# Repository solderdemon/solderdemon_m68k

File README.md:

# SolderDemon m68k

## Overview

SolderDemon develops a line of Motorola 68k computers built from **through-hole (THT) parts**. This repository holds its mainboard: the board design, firmware, software and CPLD code. Expansion boards such as the [busboard](https://github.com/solderdemon/solderdemon_m68k-busboard) plug into its J3 expansion connector.

The mainboard is built on [rosco_m68k](https://github.com/rosco-m68k/rosco_m68k) by Ross Bamford, The Really Old-School Company Limited, and contributors. SolderDemon boards carry their own revision numbers, starting at r1; the rosco r2.x numbers are the history they grew from.

## Start here

- [KiCad project](design/solderdemon_m68k.kicad_pro)
- [Schematic (PDF)](manufacturing/solderdemon_m68k-r1-schematic.pdf)
- [Build guide](docs/README.md)
- [Fabrication package](manufacturing/solderdemon_m68k-r1-factory.zip)

### Find your way around

| What you need | Where to go |
| --- | --- |
| Board design | [design](design/README.md) |
| BOM, jumper settings, memory map, and expansion pinout | [docs](docs/README.md) |
| Firmware and ROM code | [code/firmware](code/firmware) |
| PLD source and programming | [PLD guide](code/firmware/pld/README.md) |
| Software, libraries, and examples | [code/software](code/software) |
| Recommended software workflow | [rosco CLI and Docker guide](docs/development.md) |
| Emulator for rosco_m68k and rosco_6502 | [SolderDemon rosco-emulator](https://github.com/solderdemon/rosco-emulator) |

## Board views

r1 is the current through-hole prototype. KiCad renders of it, top and bottom:

The current PCB and factory files use 23 radial ceramic 100 nF capacitors with 5.08 mm
lead spacing. The renders below predate that footprint change; use the current KiCad board
for placement and hole positions.

<details>
<summary>Photos from the project's early prototypes</summary>

These images show early project prototypes.

</details>

## Hardware

### The board: r1

| | |
| --- | --- |
| CPU | MC68010, 10 MHz |
| Memory | 1 MB Flash ROM (2 × SST39SF040), 1 MB SRAM (2 × AS6C4008) |
| Glue logic | 2 × ATF1502AS CPLD in PLCC-44 sockets, programmed in circuit over JTAG (J9) |
| I/O | XR68C681 DUART: two UARTs (J1, J2), SD card over SPI (J4) |
| Expansion | 64-pin J3 connector |
| PCB | 165 × 100 mm, 4 layers |

What changed from rosco r2.42 is in the [design notes](design/README.md).

Production [CPLD firmware](code/firmware/pld/cpld/README.md) uses the r1.1 address-based ROM handoff for reliable startup. Use `code/firmware/pld/cpld/bin/ic2_decoder.jed` for IC2 and `code/firmware/pld/cpld/bin/ic3_glue.jed` for IC3; the ROM Flash image is unchanged.
The [r1 first-order sheet](docs/ORDER_R1.md) links the factory ZIP and check reports for a
five-board prototype run.

## Using the board

### Develop software

For new programs, use [rosco CLI](https://github.com/solderdemon/rosco-cli) with its Docker build workflow. It creates the current starter project, builds through Docker, and can upload and monitor over UART. Follow the [quick start](docs/development.md).

### At the bench

- Start with the [hardware build guide](design/README.md) and [bill of materials](docs/BOM.md).
- Check [power and jumper settings](docs/JUMPERS.md) before applying power, particularly JP1/JP2 for FTDI power and JP3 for Flash writes.
- Use the [J3 expansion header pinout](docs/EXPANSION.md) for peripherals. J3 is the header; JP3 is a different, two-pin jumper.
- For code builds, see the [firmware and software overview](code/README.md). The [older SD card guide](docs/legacy-sd-card.md) covers earlier board revisions and is kept for code users.

## Build and verification

### Verification

See the [r1 order sheet](docs/ORDER_R1.md) for fabrication files and check reports, and the [CPLD guide](code/firmware/pld/cpld/README.md) for the production logic and verification.

<!-- repository-layout -->
## Repository layout

- [`design/`](design/solderdemon_m68k.kicad_pro): KiCad project, schematic sheets, PCB, local libraries and design data. Open the project directly here.
- [`code/firmware/`](code/firmware/): ROM and programmable-logic sources and programming files.
- [`code/software/`](code/software/): drivers, examples and applications.
- [`code/build/`](code/build/): local build products; ignored by Git except for its README.
- [`tools/`](tools/): generators, simulations and export scripts. Run commands from the repository root unless stated otherwise.
- [`manufacturing/`](manufacturing/): fabrication packages.

Programmable-logic files are in `code/firmware/pld/`. Native CPLD tools retain their adjacent `bin/` outputs.
Design files and documentation are generated by scripts in `tools/`; change the sources and regenerate. Keep `.kicad_pro` as the source of DRC rules.
<!-- /repository-layout -->

## Licences and attribution

- **Hardware:** [CERN Open Hardware Licence v1.2](LICENCE.hardware.txt).
- **Software:** [MIT](LICENSE), with [third-party notices](licenses/README.md).
- **Documentation:** [Creative Commons Attribution 4.0](licenses/LICENSE.docs).

Based on [rosco_m68k](https://github.com/rosco-m68k/rosco_m68k) by Ross Bamford, The Really Old-School Company Limited, and contributors. SolderDemon changes include the through-hole mainboard layout, CPLD logic, board identity and build documentation. Original authorship and licence notices are retained.

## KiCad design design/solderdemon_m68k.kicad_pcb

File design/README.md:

# SolderDemon m68k through-hole mainboard design

This directory contains the SolderDemon m68k through-hole mainboard design, derived from the original [rosco_m68k](https://github.com/rosco-m68k/rosco_m68k) board. Open the [KiCad project](solderdemon_m68k.kicad_pro) to inspect the board. The schematics are split into CPU, memory, CPLDs, DUART, reset, and expansion sheets. A [schematic PDF](solderdemon_m68k.pdf) is included for quick reading.

## Build references

1. Review the [bill of materials](../docs/BOM.md). Its source is the [KiCad CSV export](solderdemon_m68k.csv); confirm each footprint and package before ordering.
2. Read [jumper and power notes](../docs/JUMPERS.md) before applying power or connecting an SD card.
3. Use the [J3 expansion pinout](../docs/EXPANSION.md) when making an expansion board. **J3** is the expansion connector; **JP3** is the Flash write-enable jumper.
4. For an r1 PCB order, follow the [first-order sheet](../docs/ORDER_R1.md) and use the [r1 factory ZIP](../manufacturing/solderdemon_m68k-r1-factory.zip). Its Gerbers and drills are generated from the current board; the [DRC report](../manufacturing/solderdemon_m68k-r1-drc.rpt), [ERC report](../manufacturing/solderdemon_m68k-r1-erc.rpt), [schematic PDF](../manufacturing/solderdemon_m68k-r1-schematic.pdf), and [BOM](../manufacturing/solderdemon_m68k-r1-bom.csv) are alongside it. Regenerate all of them after any design change.

## Contents

- Schematic sheets, PCB, project, local symbols and footprints are directly in this directory.
- [`../tools/`](../tools/): design generators, simulations and exports.
- [`../manufacturing/`](../manufacturing/): Gerbers, drills, fabrication ZIP, BOM, PDF and reports.
- [`../docs/`](../docs/README.md): assembly and reference documentation.

## r1: SolderDemon numbering, the DUART in the CPLD column

From here on the board carries its own revision numbers, starting at **r1**; the r2.x numbers
below are the rosco_m68k history it grew from.

r1 puts the three PLCC-44 sockets in one column: IC3 (glue), IC2 (decoder) and the DUART IC4
under them. IC4 used to sit 8 mm to the right, and moving it left would have put its pins on the
RAM U4, so the board is 5 mm longer instead (165 × 100 mm). `tools/r1_layout.py` stretches the
r2.42 board along a cut between the CPLDs and the CPU/RAM: everything right of the cut moves 5 mm
right, tracks crossing the cut get a horizontal bridge, so no clearance shrinks. IC4 then moves
into the column, its decoupling cap C22 into the space it left, and the DUART is routed again.
The upstream badges (WEEE bin, OSHW block, rosco_m68k logos, GitHub URL) are gone from the
silkscreen (`tools/strip_silk.py`). The CPU decoupling C20/C12/C29/C31 stands in an even column in the gap the stretch
opened, and the back carries the SolderDemon identity as on the busboard: the logo, the name and
"M68K Computer r1" (`tools/r1_identity.py`). All silkscreen text is in KiCad's own font; the
Futura that r2.x asked for is not installed and made KiCad stop at a message box.

## First r1 prototype order

The r1 board is **165 × 100 mm, four copper layers**. Generate the order package with
KiCad 10 Python from the repository root:

```sh
"/c/Program Files/KiCad/10.0/bin/python.exe" tools/export_r1.py
```

The script gates on zero ERC/DRC errors and zero unconnected pads, then replaces the files in
`manufacturing/`. Send only `solderdemon_m68k-r1-factory.zip` to the PCB manufacturer;
it contains the four copper layers, both masks, both silkscreens, outline, and PTH/NPTH drills.
For the first run, order **five bare PCBs** and populate one after checking the physical fit of
the three PLCC-44 sockets, JTAG header orientation, and other chosen components. The CSV BOM
is a design list; choose and verify supplier parts before buying components.

The existing route was improved for `D6` and `A18` with `tools/optimize_r1_routes.py`.
That script accepts a shorter route only when it uses no more vias and KiCad DRC remains clean.
Run the export script again if any routing or silkscreen changes are made.

## Revision 2.42: finished CPLD mainboard

r2.42 removes the J6 address/EXPSEL breakout and the J7 SPI CS2 breakout. Their unused copper
branches are pruned and the affected A1/FC2 routes are reconnected. Sixteen narrow VCC bridge
segments are widened from 0.2 to 0.3 mm. The board and all schematic title blocks carry revision
2.42; the crowded UART pin text and obsolete header labels are removed from the silkscreen.

## Revision 2.14: two ATF1502AS instead of four GALs

r2.14 replaces the four ATF22V10C GALs (IC2, IC3, IC5, IC6) with two ATF1502AS-10JU44 CPLDs in
through-hole PLCC-44 sockets, programmed in circuit through the JTAG header **J9**. The logic and
its check are described in [code/firmware/pld/cpld](../code/firmware/pld/cpld/README.md). Both sockets sit one above
the other where the three glue GALs stood; the old IC2 gap between the CPU and the ROMs is 24.4 mm
and a socket is 24.6 mm. J8, R31, R32 and R16 moved left to make room; the old GAL
decoupling C23-C25 and the DUART's C27/C28 now stand in one column under J9, and C33 is new.

r2.13 was drawn by hand, so r2.42 is an *edit* of it made by scripts, always starting
again from the r2.13 board in git. To rebuild it (KiCad 10, Docker for the fitter):

```sh
K="/c/Program Files/KiCad/10.0/bin"
./code/firmware/pld/cpld/build.sh                  # 1. *.pld -> bin/*.jed, pins checked against the source
python3 tools/verify_cpld.py       # 2. GAL decode/glue + address-based BOOT reference
python tools/cpld_sch.py           # 3. CPLDs sheet of the schematic, from the PIN lines
"$K/python.exe" tools/cpld_board.py   # 4. GALs out, sockets/J9/caps in, nets from the schematic
"$K/python.exe" tools/cpld_route.py   # 5. routing with KiCadRoutingTools, planes, cleanup
"$K/python.exe" tools/remove_access_headers.py # 6. remove J6/J7 and set revision 2.42
"$K/python.exe" tools/cpld_route.py --finish     # 7. prune obsolete header branches
"$K/python.exe" tools/repair_dangling.py        # 8. remove the remaining old stubs
"$K/python.exe" tools/cpld_route.py             # 9. reconnect affected nets
"$K/python.exe" tools/repair_dangling.py        # 10. repeat for residual stubs
"$K/python.exe" tools/cpld_route.py             # 11. finish the reconnection
"$K/python.exe" tools/polish_board.py           # 12. wider VCC bridges, clean silkscreen
"$K/python.exe" tools/brand_project.py          # 13. apply SolderDemon m68k project branding
python tools/strip_silk.py                      # 14. upstream badges off the silkscreen
"$K/python.exe" tools/r1_layout.py              # 15. r1: longer board, DUART into the column
"$K/python.exe" tools/cpld_route.py             # 16. route the DUART again
"$K/python.exe" tools/trim_stubs.py             # 17. cut router overshoots back to their junctions
python tools/make_logo.py 17                    # 18. SolderDemon logo footprint, as on the busboard
"$K/python.exe" tools/r1_identity.py            # 19. CPU decoupling column, SolderDemon identity on the back
"$K/python.exe" tools/cpld_route.py             # 20. route what the column tore up
"$K/python.exe" tools/trim_stubs.py             # 21. and trim again
"$K/python.exe" tools/ceramic_decouplers.py      # 22. 23 radial ceramic 100 nF, 5.08 mm pitch
"$K/python.exe" tools/cpld_route.py             # 23. reconnect copper displaced by larger caps
"$K/python.exe" tools/trim_stubs.py             # 24. trim router overshoots
"$K/python.exe" tools/cpld_route.py             # 25. reconnect any net opened by trimming
"$K/python.exe" tools/r1_tidy.py                 # 26. LED caps, jumper block, resistor labels, copper r1 mark
"$K/python.exe" tools/cpld_route.py             # 27. reconnect the copper the tidy-up displaced
"$K/python.exe" tools/trim_stubs.py             # 28. trim router overshoots
"$K/python.exe" tools/r1_restore_trace_widths.py # 29. remove redundant wide power traces
"$K/kicad-cli.exe" pcb drc --schematic-parity design/solderdemon_m68k.kicad_pcb
```

The 5.08 mm capacitor conversion is the current r1 layout. It updates the footprint fields in
the older hand-drawn sheets, replaces all 23 board footprints while keeping each VCC pad close
to its original position, and moves parts locally to leave at least 0.5 mm between courtyards
or imported package outlines. Each reference is centred inside a compact 4.4 x 2.6 mm
silkscreen outline; the outline opens around the leads so it does not print across the solder
pads. The fabrication and courtyard layers retain the maximum body dimensions of KEMET
C322C104K5R5TA as a reference; verify the selected
yellow capacitor against it before ordering. Generate the CAM package again after the final DRC.

`r1_tidy.py` is the last placement step. It stands C6 and C32 upright on the LED centre line,
C32 halfway between LED1 and LED2 and C6 the same distance to the left; puts C17, the
"Jumper Settings" frame and C8 on one centre line halfway between the CPU's pin row and the
ROM frames, with equal gaps between them; centres every 0207 resistor reference inside its
body outline; and marks the revision the SolderDemon 6502 way, as 2.5 mm copper "r1" under the
mask in the top left corner. The silkscreen "Revision r1" goes; the copyright line moves to the
back under "M68K Computer r1", and "SolderDemon m68k" stands above the CPU on the front, lettered as
on the back. The copper-to-edge rule in `solderdemon_m68k.kicad_pro` is 0.3 mm, so the inner
GND and VCC planes stop 0.3 mm short of the routed outline.

`r1_restore_trace_widths.py` removes the 2 mm VCC/GND overlays around J5, C21,
C16 and H4 and the 1.6 mm VCC branch near C3. The 0.85 mm connections inherited
from Rosco r2 remain. Run it after the last routing and stub trimming pass, then
check the refilled board with DRC.

Steps 5, 9 and 11 use [KiCadRoutingTools](https://github.com/drandyhaas/KiCadRoutingTools) from the
workspace's `tools/KiCadRoutingTools` (set `KRT` to use another clone); its logs go to
`design/routing/`. `tools/check_board.py` prints the DRC of any board with its
zones refilled.

The hardware design is licensed under [CERN OHL v1.2](../LICENCE.hardware.txt). The documentation is attributed in the [repository README](../README.md).

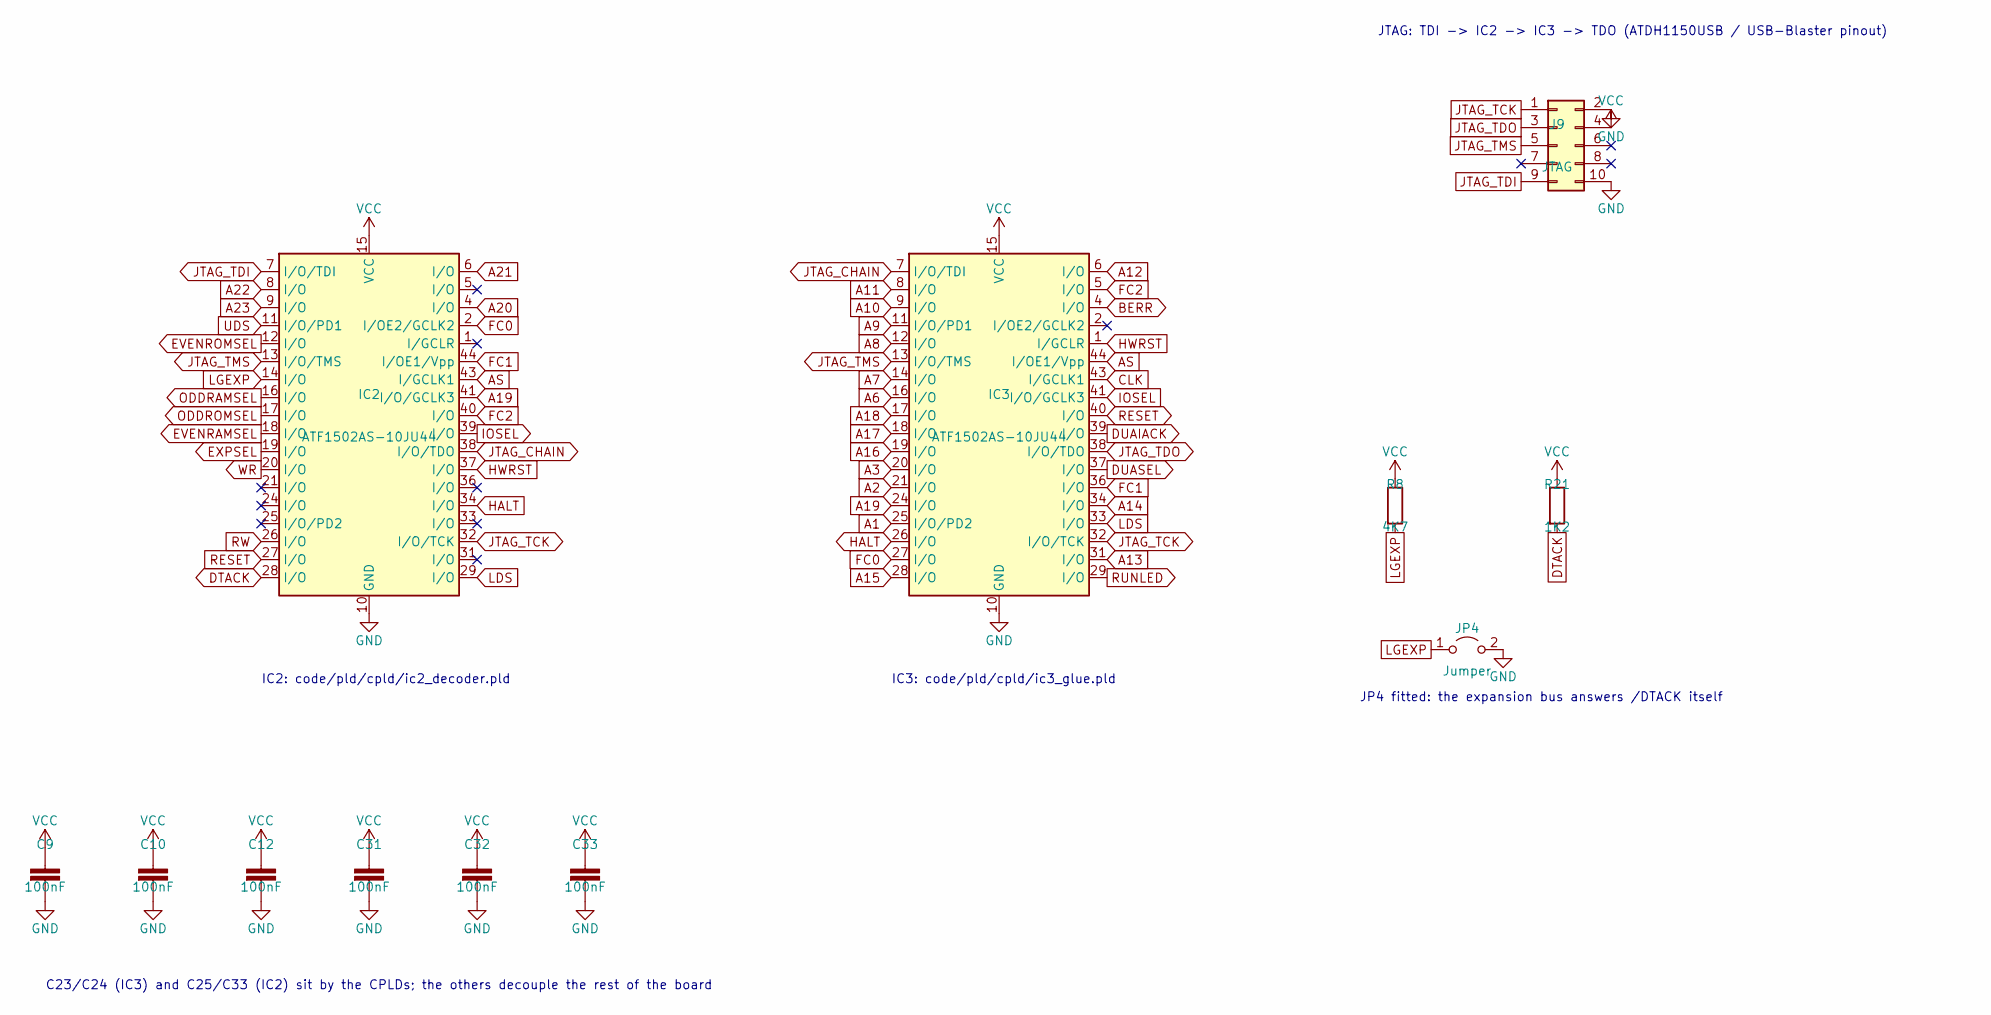
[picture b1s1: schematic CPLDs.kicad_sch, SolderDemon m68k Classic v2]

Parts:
C9, C10, C12, C31, C32, C33: 100nF; C_Radial_5.08mm
IC2, IC3: ATF1502AS-10JU44; PLCC-44_THT-Socket
J9: JTAG; PinHeader_2x05_P2.54mm_Vertical
JP4: Jumper; 1X02
R8: 4K7; 0207_10
R21: 1K2; 0207_10

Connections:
A1: IC3.25 (I/O/PD2); also elsewhere on the board
A2: IC3.21 (I/O); also elsewhere on the board
A3: IC3.20 (I/O); also elsewhere on the board
A6: IC3.16 (I/O); also elsewhere on the board
A7: IC3.14 (I/O); also elsewhere on the board
A8: IC3.12 (I/O); also elsewhere on the board
A9: IC3.11 (I/O/PD1); also elsewhere on the board
A10: IC3.9 (I/O); also elsewhere on the board
A11: IC3.8 (I/O); also elsewhere on the board
A12: IC3.6 (I/O); also elsewhere on the board
A13: IC3.31 (I/O); also elsewhere on the board
A14: IC3.34 (I/O); also elsewhere on the board
A15: IC3.28 (I/O); also elsewhere on the board
A16: IC3.19 (I/O); also elsewhere on the board
A17: IC3.18 (I/O); also elsewhere on the board
A18: IC3.17 (I/O); also elsewhere on the board
A19: IC2.41 (I/O/GCLK3), IC3.24 (I/O); also elsewhere on the board
A20: IC2.4 (I/O); also elsewhere on the board
A21: IC2.6 (I/O); also elsewhere on the board
A22: IC2.8 (I/O); also elsewhere on the board
A23: IC2.9 (I/O); also elsewhere on the board
AS: IC2.43 (I/GCLK1), IC3.44 (I/OE1/Vpp); also elsewhere on the board
BERR: IC3.4 (I/O); also elsewhere on the board
CLK: IC3.43 (I/GCLK1); also elsewhere on the board
DTACK: IC2.28 (I/O), R21.2; also elsewhere on the board
DUAIACK: IC3.39 (I/O); also elsewhere on the board
DUASEL: IC3.37 (I/O); also elsewhere on the board
EVENRAMSEL: IC2.18 (I/O); also elsewhere on the board
EVENROMSEL: IC2.12 (I/O); also elsewhere on the board
EXPSEL: IC2.19 (I/O); also elsewhere on the board
FC0: IC2.2 (I/OE2/GCLK2), IC3.27 (I/O); also elsewhere on the board
FC1: IC2.44 (I/OE1/Vpp), IC3.36 (I/O); also elsewhere on the board
FC2: IC2.40 (I/O), IC3.5 (I/O); also elsewhere on the board
GND: C9.2, C10.2, C12.2, C31.2, C32.2, C33.2, IC2.10 (GND), IC2.22 (GND), IC2.30 (GND), IC2.42 (GND), IC3.10 (GND), IC3.22 (GND), IC3.30 (GND), IC3.42 (GND), J9.2, J9.10, JP4.2 (B); also elsewhere on the board
HALT: IC2.34 (I/O), IC3.26 (I/O); also elsewhere on the board
HWRST: IC2.37 (I/O), IC3.1 (I/GCLR); also elsewhere on the board
IOSEL: IC2.39 (I/O), IC3.41 (I/O/GCLK3); also elsewhere on the board
JTAG_CHAIN: IC2.38 (I/O/TDO), IC3.7 (I/O/TDI)
JTAG_TCK: IC2.32 (I/O/TCK), IC3.32 (I/O/TCK), J9.1
JTAG_TDI: IC2.7 (I/O/TDI), J9.9
JTAG_TDO: IC3.38 (I/O/TDO), J9.3
JTAG_TMS: IC2.13 (I/O/TMS), IC3.13 (I/O/TMS), J9.5
LDS: IC2.29 (I/O), IC3.33 (I/O); also elsewhere on the board
LGEXP: IC2.14 (I/O), JP4.1 (A), R8.2
ODDRAMSEL: IC2.16 (I/O); also elsewhere on the board
ODDROMSEL: IC2.17 (I/O); also elsewhere on the board
RESET: IC2.27 (I/O), IC3.40 (I/O); also elsewhere on the board
RUNLED: IC3.29 (I/O); also elsewhere on the board
RW: IC2.26 (I/O); also elsewhere on the board
UDS: IC2.11 (I/O/PD1); also elsewhere on the board
VCC: C9.1, C10.1, C12.1, C31.1, C32.1, C33.1, IC2.3 (VCC), IC2.15 (VCC), IC2.23 (VCC), IC2.35 (VCC), IC3.3 (VCC), IC3.15 (VCC), IC3.23 (VCC), IC3.35 (VCC), J9.4, R8.1, R21.1; also elsewhere on the board
WR: IC2.20 (I/O); also elsewhere on the board

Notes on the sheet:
IC2: code/pld/cpld/ic2_decoder.pld
IC3: code/pld/cpld/ic3_glue.pld
JTAG: TDI -> IC2 -> IC3 -> TDO (ATDH1150USB / USB-Blaster pinout)
C23/C24 (IC3) and C25/C33 (IC2) sit by the CPLDs; the others decouple the rest of the board
JP4 fitted: the expansion bus answers /DTACK itself

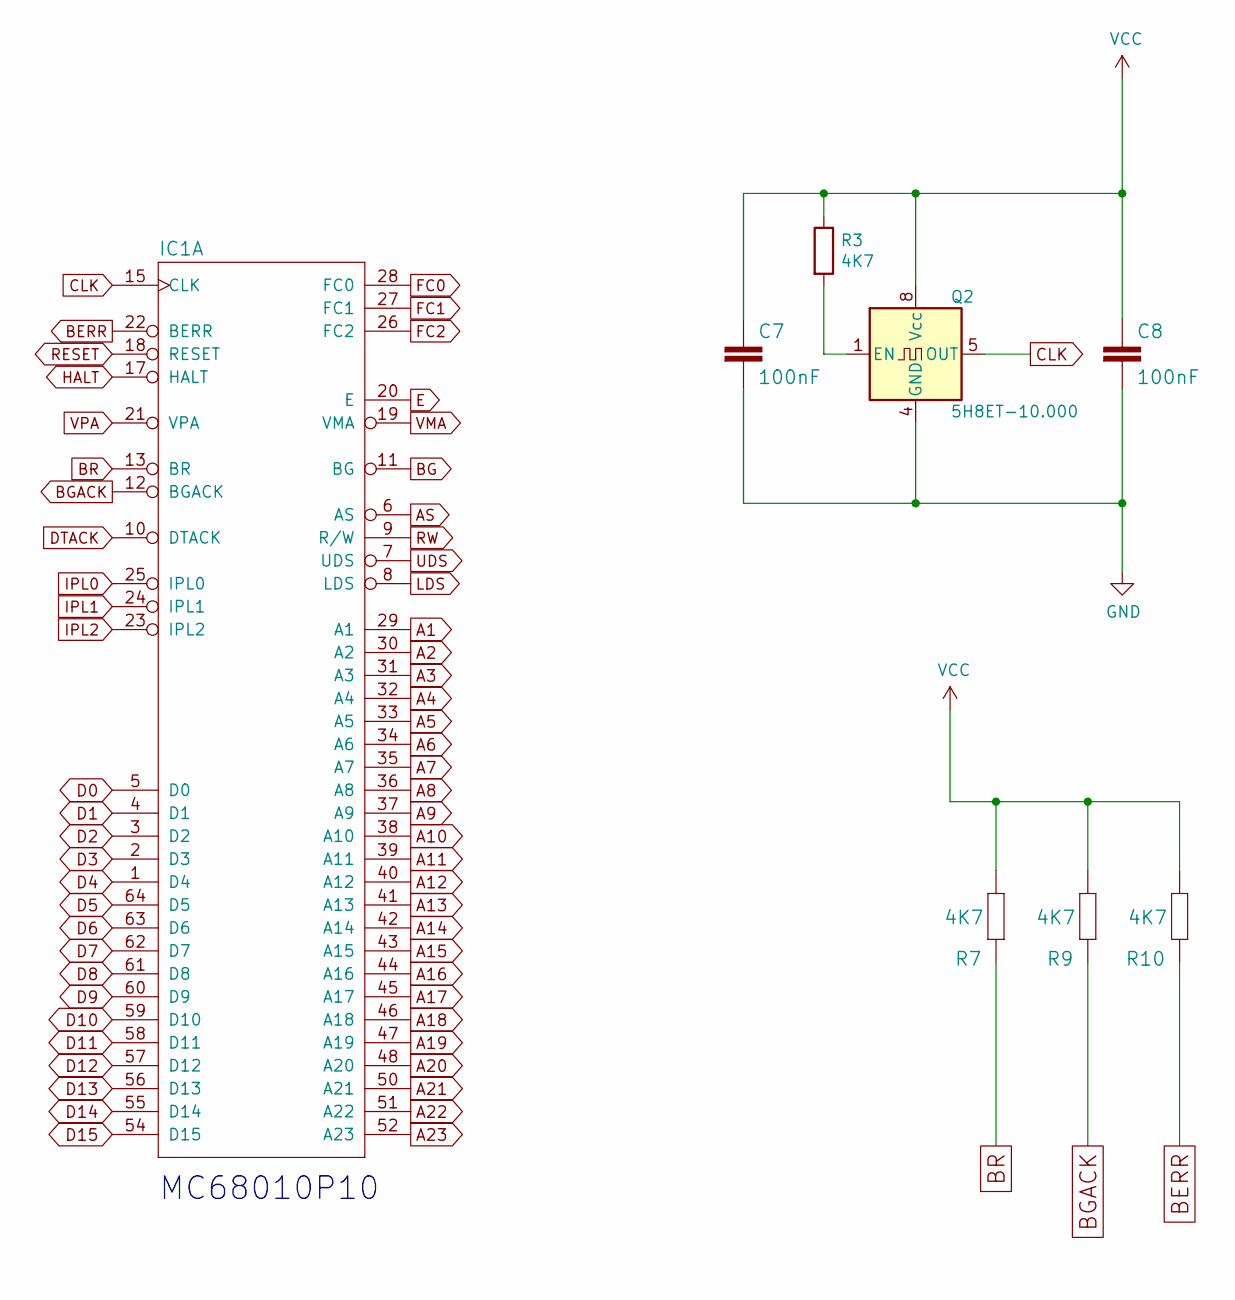
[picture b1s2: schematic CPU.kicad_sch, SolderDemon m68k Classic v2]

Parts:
C7, C8: 100nF; C_Radial_5.08mm
IC1: MC68010P10; DIL64
Q2: 5H8ET-10.000; Oscillator_DIP-8
R3, R7, R9, R10: 4K7; 0207_10

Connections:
A1: IC1.29 (A1); also elsewhere on the board
A2: IC1.30 (A2); also elsewhere on the board
A3: IC1.31 (A3); also elsewhere on the board
A4: IC1.32 (A4); also elsewhere on the board
A5: IC1.33 (A5); also elsewhere on the board
A6: IC1.34 (A6); also elsewhere on the board
A7: IC1.35 (A7); also elsewhere on the board
A8: IC1.36 (A8); also elsewhere on the board
A9: IC1.37 (A9); also elsewhere on the board
A10: IC1.38 (A10); also elsewhere on the board
A11: IC1.39 (A11); also elsewhere on the board
A12: IC1.40 (A12); also elsewhere on the board
A13: IC1.41 (A13); also elsewhere on the board
A14: IC1.42 (A14); also elsewhere on the board
A15: IC1.43 (A15); also elsewhere on the board
A16: IC1.44 (A16); also elsewhere on the board
A17: IC1.45 (A17); also elsewhere on the board
A18: IC1.46 (A18); also elsewhere on the board
A19: IC1.47 (A19); also elsewhere on the board
A20: IC1.48 (A20); also elsewhere on the board
A21: IC1.50 (A21); also elsewhere on the board
A22: IC1.51 (A22); also elsewhere on the board
A23: IC1.52 (A23); also elsewhere on the board
AS: IC1.6 (AS); also elsewhere on the board
BERR: IC1.22 (BERR), R10.1; also elsewhere on the board
BG: IC1.11 (BG); also elsewhere on the board
BGACK: IC1.12 (BGACK), R9.1; also elsewhere on the board
BR: IC1.13 (BR), R7.1; also elsewhere on the board
CLK: IC1.15 (CLK), Q2.5 (OUT); also elsewhere on the board
D0: IC1.5 (D0); also elsewhere on the board
D1: IC1.4 (D1); also elsewhere on the board
D2: IC1.3 (D2); also elsewhere on the board
D3: IC1.2 (D3); also elsewhere on the board
D4: IC1.1 (D4); also elsewhere on the board
D5: IC1.64 (D5); also elsewhere on the board
D6: IC1.63 (D6); also elsewhere on the board
D7: IC1.62 (D7); also elsewhere on the board
D8: IC1.61 (D8); also elsewhere on the board
D9: IC1.60 (D9); also elsewhere on the board
D10: IC1.59 (D10); also elsewhere on the board
D11: IC1.58 (D11); also elsewhere on the board
D12: IC1.57 (D12); also elsewhere on the board
D13: IC1.56 (D13); also elsewhere on the board
D14: IC1.55 (D14); also elsewhere on the board
D15: IC1.54 (D15); also elsewhere on the board
DTACK: IC1.10 (DTACK); also elsewhere on the board
E: IC1.20 (E); also elsewhere on the board
FC0: IC1.28 (FC0); also elsewhere on the board
FC1: IC1.27 (FC1); also elsewhere on the board
FC2: IC1.26 (FC2); also elsewhere on the board
GND: C7.2, C8.2, Q2.4 (GND); also elsewhere on the board
HALT: IC1.17 (HALT); also elsewhere on the board
IPL0: IC1.25 (IPL0); also elsewhere on the board
IPL1: IC1.24 (IPL1); also elsewhere on the board
IPL2: IC1.23 (IPL2); also elsewhere on the board
LDS: IC1.8 (LDS); also elsewhere on the board
unnamed: Q2.1 (EN), R3.2
RESET: IC1.18 (RESET); also elsewhere on the board
RW: IC1.9 (R/W); also elsewhere on the board
UDS: IC1.7 (UDS); also elsewhere on the board
VCC: C7.1, C8.1, Q2.8 (Vcc), R3.1, R7.2, R9.2, R10.2; also elsewhere on the board
VMA: IC1.19 (VMA); also elsewhere on the board
VPA: IC1.21 (VPA); also elsewhere on the board

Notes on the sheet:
MC68010P10

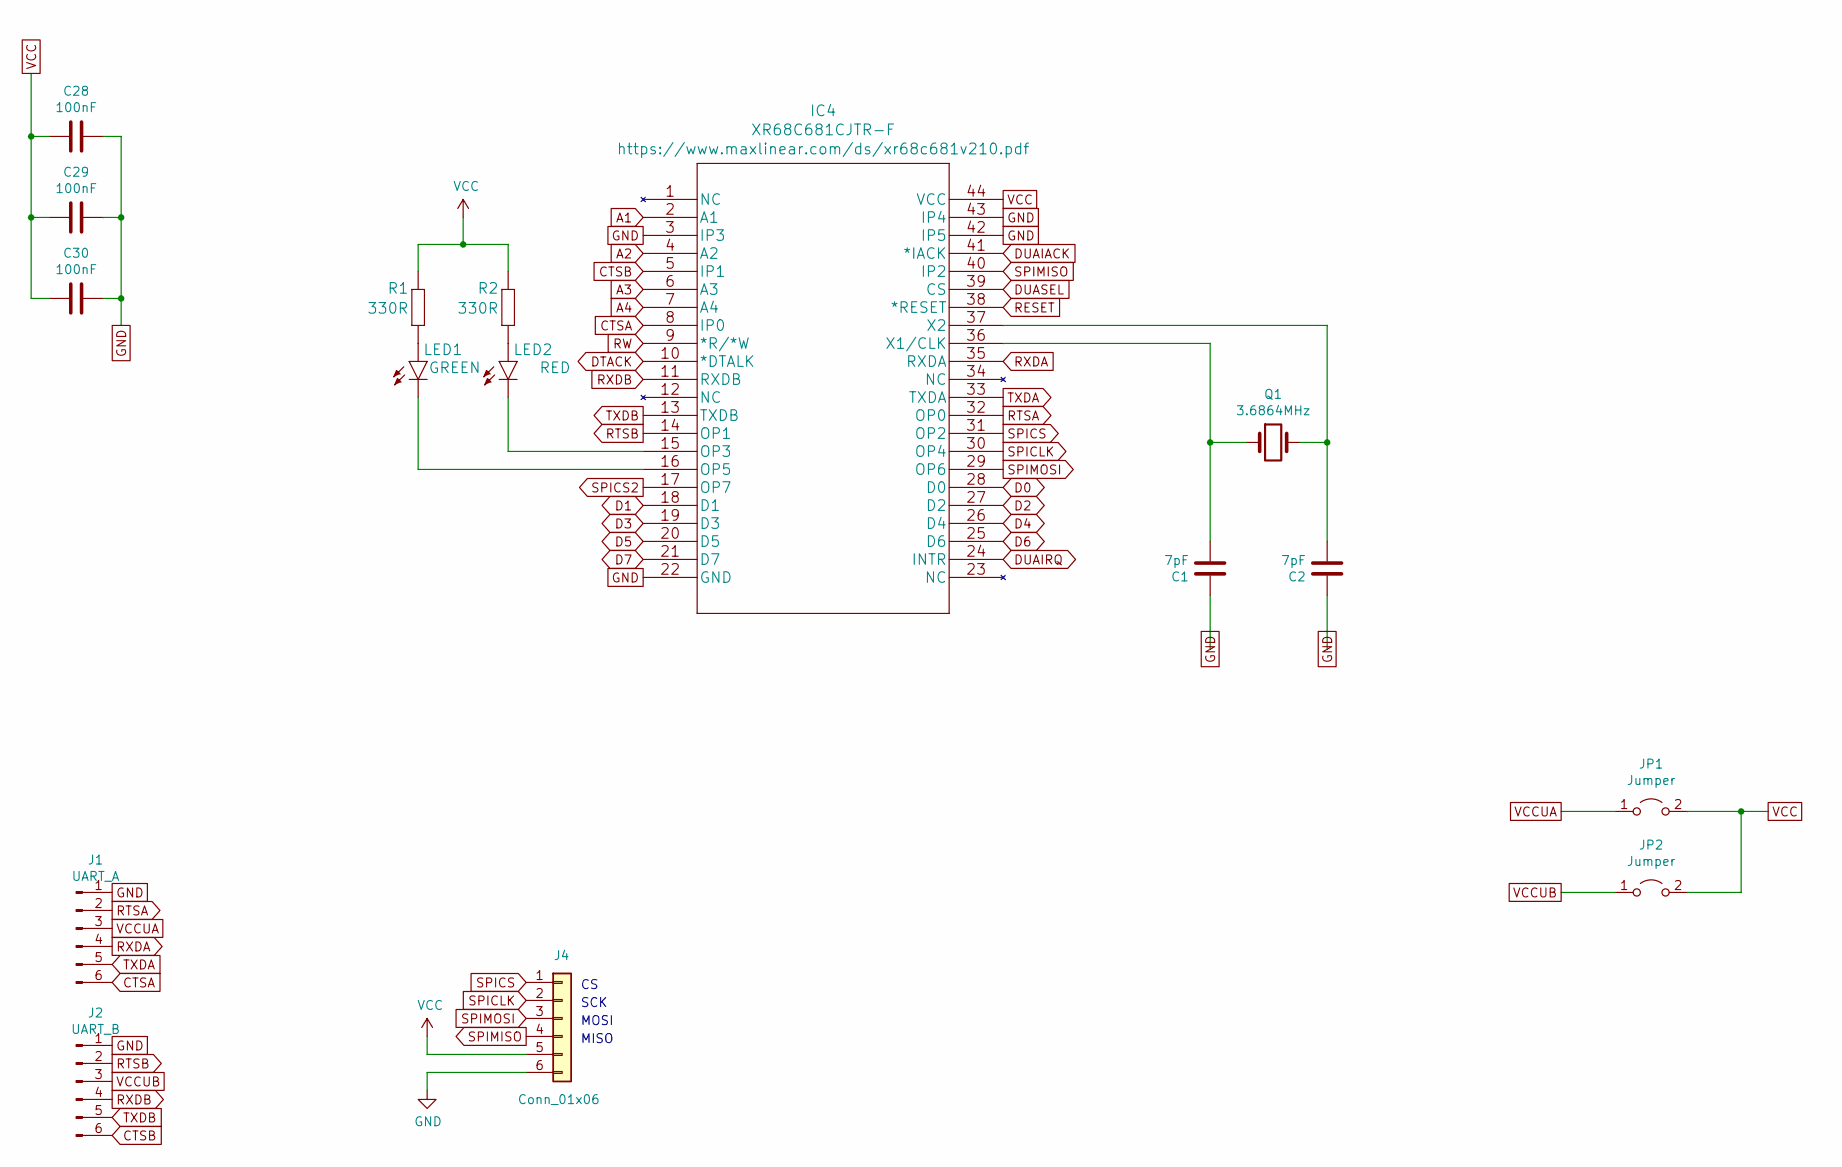
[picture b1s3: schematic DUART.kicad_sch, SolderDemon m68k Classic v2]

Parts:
C1, C2: 7pF; C2.5_or_3.5-3
C28, C29, C30: 100nF; C_Radial_5.08mm
IC4: XR68C681CJTR-F; PLCC-44_THT-Socket
J1: UART_A; 1X06
J2: UART_B; 1X06
J4: Conn_01x06; 1X06
JP1, JP2: Jumper; 1X02
LED1: GREEN; LED5MM
LED2: RED; LED5MM
Q1: 3.6864MHz; Crystal_HC49-4H_Vertical
R1, R2: 330R; 0207_10

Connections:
A1: IC4.2 (A1); also elsewhere on the board
A2: IC4.4 (A2); also elsewhere on the board
A3: IC4.6 (A3); also elsewhere on the board
A4: IC4.7 (A4); also elsewhere on the board
CTSA: IC4.8 (IP0), J1.6
CTSB: IC4.5 (IP1), J2.6
D0: IC4.28 (D0); also elsewhere on the board
D1: IC4.18 (D1); also elsewhere on the board
D2: IC4.27 (D2); also elsewhere on the board
D3: IC4.19 (D3); also elsewhere on the board
D4: IC4.26 (D4); also elsewhere on the board
D5: IC4.20 (D5); also elsewhere on the board
D6: IC4.25 (D6); also elsewhere on the board
D7: IC4.21 (D7); also elsewhere on the board
DTACK: IC4.10 (*DTALK); also elsewhere on the board
DUAIACK: IC4.41 (*IACK); also elsewhere on the board
DUAIRQ: IC4.24 (INTR); also elsewhere on the board
DUASEL: IC4.39 (CS); also elsewhere on the board
GND: C1.1, C2.1, C28.1, C29.1, C30.1, IC4.3 (IP3), IC4.22 (GND), IC4.42 (IP5), IC4.43 (IP4), J1.1, J2.1, J4.6; also elsewhere on the board
unnamed: IC4.15 (OP3), LED2.K (C)
unnamed: IC4.16 (OP5), LED1.K (C)
unnamed: C1.2, IC4.36 (X1/CLK), Q1.1
unnamed: C2.2, IC4.37 (X2), Q1.2
unnamed: LED1.A, R1.1
unnamed: LED2.A, R2.1
RESET: IC4.38 (*RESET); also elsewhere on the board
RTSA: IC4.32 (OP0), J1.2
RTSB: IC4.14 (OP1), J2.2
RW: IC4.9 (*R/*W); also elsewhere on the board
RXDA: IC4.35 (RXDA), J1.4
RXDB: IC4.11 (RXDB), J2.4
SPICLK: IC4.30 (OP4), J4.2
SPICS: IC4.31 (OP2), J4.1
SPICS2: IC4.17 (OP7)
SPIMISO: IC4.40 (IP2), J4.4
SPIMOSI: IC4.29 (OP6), J4.3
TXDA: IC4.33 (TXDA), J1.5
TXDB: IC4.13 (TXDB), J2.5
VCC: C28.2, C29.2, C30.2, IC4.44 (VCC), J4.5, JP1.2 (B), JP2.2 (B), R1.2, R2.2; also elsewhere on the board
VCCUA: J1.3, JP1.1 (A)
VCCUB: J2.3, JP2.1 (A)

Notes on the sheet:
MISO
SCK
MOSI

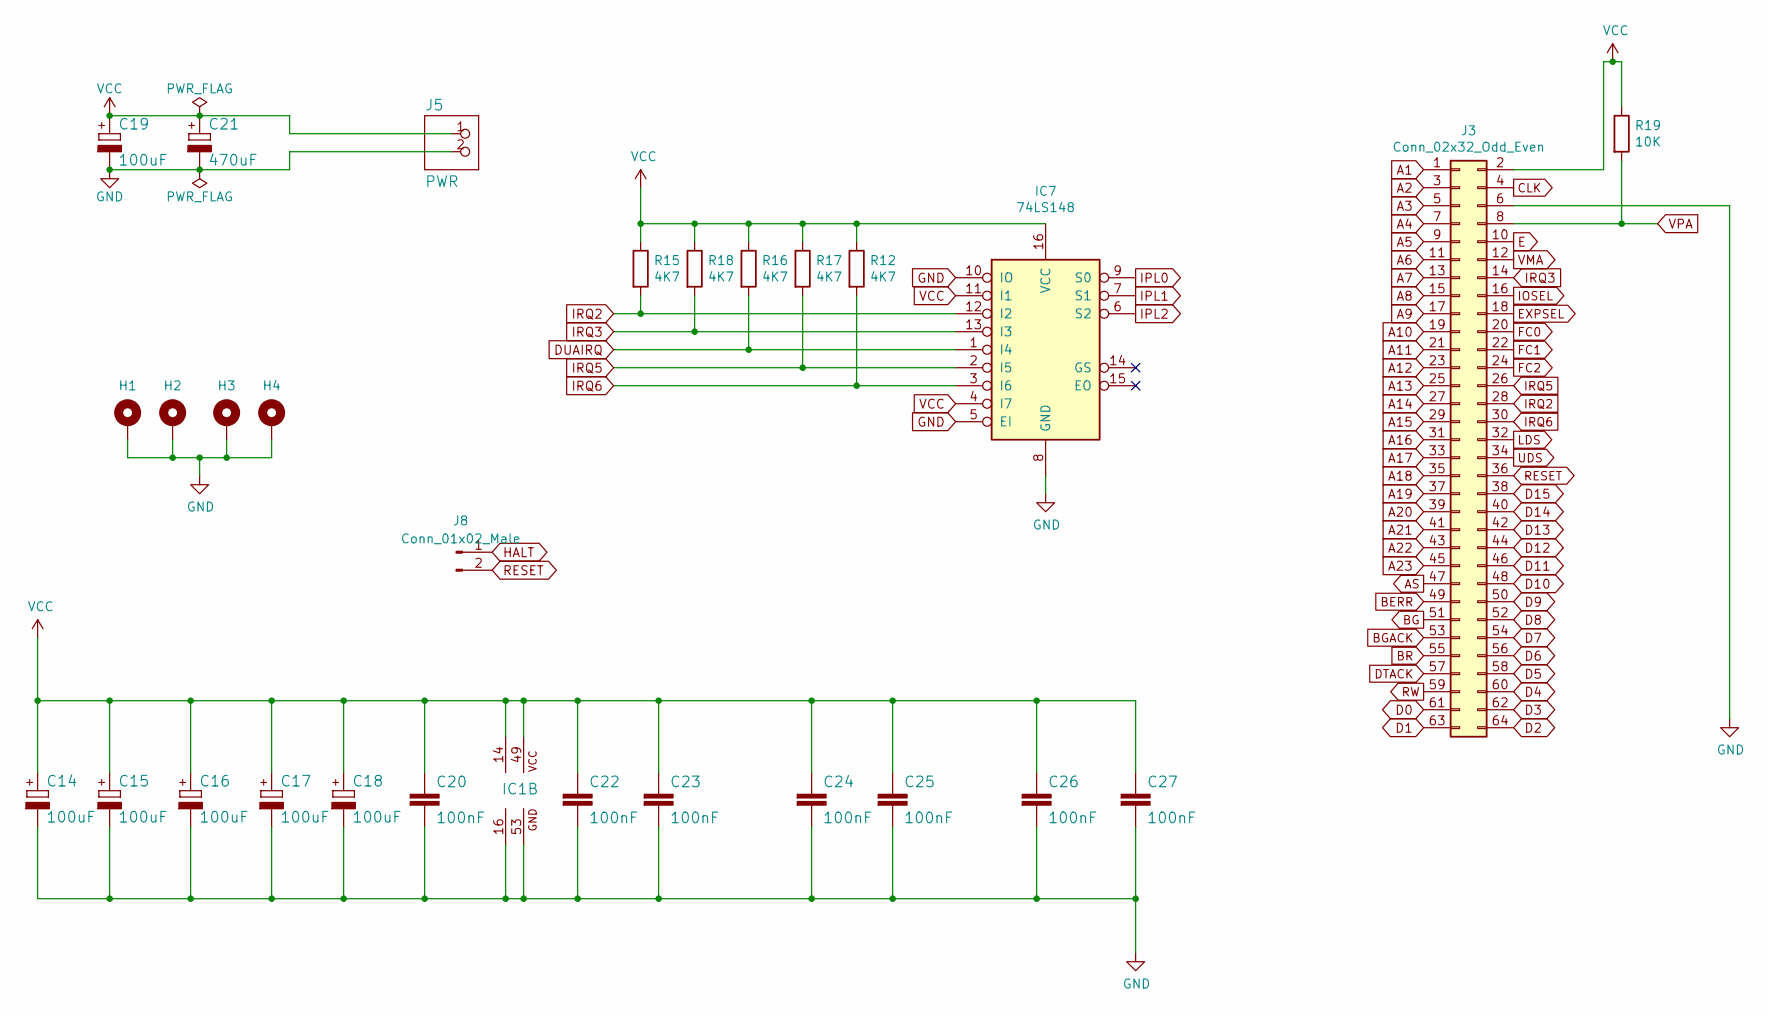
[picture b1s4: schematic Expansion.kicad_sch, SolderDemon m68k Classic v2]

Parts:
C14, C15, C16, C17, C18, C19: 100uF; E2,5-5
C20, C22, C23, C24, C25, C26, C27: 100nF; C_Radial_5.08mm
C21: 470uF; E3,5-10
H1, H2, H3, H4: MountingHole; MountingHole_3.2mm_M3_Pad
IC1: MC68010P10; DIL64
IC7: 74LS148; DIP-16_W7.62mm_LongPads
J3: Conn_02x32_Odd_Even; PinHeader_2x32_P2.54mm_Vertical
J5: PWR; 1X02
J8: Conn_01x02_Male; PinHeader_1x02_P2.54mm_Vertical
R12, R15, R16, R17, R18: 4K7; 0207_10
R19: 10K; 0207_10

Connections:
A1: J3.1; also elsewhere on the board
A2: J3.3; also elsewhere on the board
A3: J3.5; also elsewhere on the board
A4: J3.7; also elsewhere on the board
A5: J3.9; also elsewhere on the board
A6: J3.11; also elsewhere on the board
A7: J3.13; also elsewhere on the board
A8: J3.15; also elsewhere on the board
A9: J3.17; also elsewhere on the board
A10: J3.19; also elsewhere on the board
A11: J3.21; also elsewhere on the board
A12: J3.23; also elsewhere on the board
A13: J3.25; also elsewhere on the board
A14: J3.27; also elsewhere on the board
A15: J3.29; also elsewhere on the board
A16: J3.31; also elsewhere on the board
A17: J3.33; also elsewhere on the board
A18: J3.35; also elsewhere on the board
A19: J3.37; also elsewhere on the board
A20: J3.39; also elsewhere on the board
A21: J3.41; also elsewhere on the board
A22: J3.43; also elsewhere on the board
A23: J3.45; also elsewhere on the board
AS: J3.47; also elsewhere on the board
BERR: J3.49; also elsewhere on the board
BG: J3.51; also elsewhere on the board
BGACK: J3.53; also elsewhere on the board
BR: J3.55; also elsewhere on the board
CLK: J3.4; also elsewhere on the board
D0: J3.61; also elsewhere on the board
D1: J3.63; also elsewhere on the board
D2: J3.64; also elsewhere on the board
D3: J3.62; also elsewhere on the board
D4: J3.60; also elsewhere on the board
D5: J3.58; also elsewhere on the board
D6: J3.56; also elsewhere on the board
D7: J3.54; also elsewhere on the board
D8: J3.52; also elsewhere on the board
D9: J3.50; also elsewhere on the board
D10: J3.48; also elsewhere on the board
D11: J3.46; also elsewhere on the board
D12: J3.44; also elsewhere on the board
D13: J3.42; also elsewhere on the board
D14: J3.40; also elsewhere on the board
D15: J3.38; also elsewhere on the board
DTACK: J3.57; also elsewhere on the board
DUAIRQ: IC7.1 (I4), R16.2; also elsewhere on the board
E: J3.10; also elsewhere on the board
EXPSEL: J3.18; also elsewhere on the board
FC0: J3.20; also elsewhere on the board
FC1: J3.22; also elsewhere on the board
FC2: J3.24; also elsewhere on the board
GND: C14.-, C15.-, C16.-, C17.-, C18.-, C19.-, C20.2, C21.-, C22.2, C23.2, C24.2, C25.2, C26.2, C27.2, H1.1, H2.1, H3.1, H4.1, IC1.16 (GND@1), IC1.53 (GND@2), IC7.5 (EI), IC7.8 (GND), IC7.10 (IO), J3.6, J5.2; also elsewhere on the board
HALT: J8.1; also elsewhere on the board
IOSEL: J3.16; also elsewhere on the board
IPL0: IC7.9 (S0); also elsewhere on the board
IPL1: IC7.7 (S1); also elsewhere on the board
IPL2: IC7.6 (S2); also elsewhere on the board
IRQ2: IC7.12 (I2), J3.28, R15.2
IRQ3: IC7.13 (I3), J3.14, R18.2
IRQ5: IC7.2 (I5), J3.26, R17.2
IRQ6: IC7.3 (I6), J3.30, R12.2
LDS: J3.32; also elsewhere on the board
RESET: J3.36, J8.2; also elsewhere on the board
RW: J3.59; also elsewhere on the board
UDS: J3.34; also elsewhere on the board
VCC: C14.+, C15.+, C16.+, C17.+, C18.+, C19.+, C20.1, C21.+, C22.1, C23.1, C24.1, C25.1, C26.1, C27.1, IC1.14 (VCC@1), IC1.49 (VCC@2), IC7.4 (I7), IC7.11 (I1), IC7.16 (VCC), J3.2, J5.1, R12.1, R15.1, R16.1, R17.1, R18.1, R19.1; also elsewhere on the board
VMA: J3.12; also elsewhere on the board
VPA: J3.8, R19.2; also elsewhere on the board

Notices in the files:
design/CPLDs.kicad_sch:
Open Source Hardware licenced under CERN Open Hardware Licence
Copyright 2019-2026 Ross Bamford and Contributors
design/CPU.kicad_sch:
Copyright 2019-2023 Ross Bamford and Contributors
design/solderdemon_m68k.kicad_pcb:
Copyright ©2019-2026 Ross Bamford & Contributors
© 2019-2026 SolderDemon
